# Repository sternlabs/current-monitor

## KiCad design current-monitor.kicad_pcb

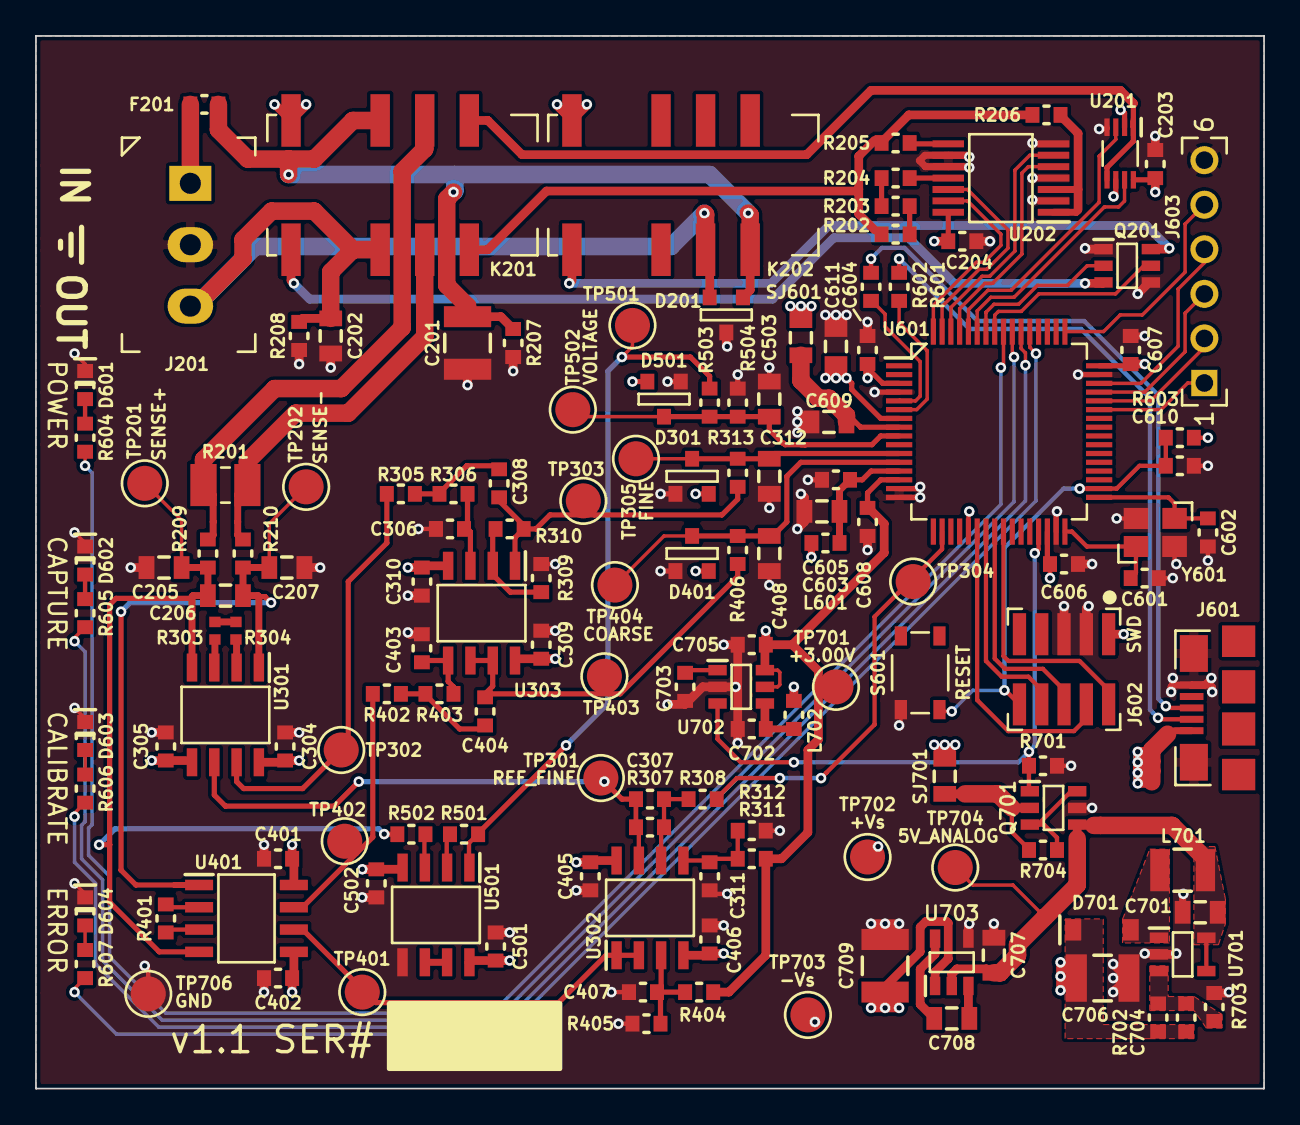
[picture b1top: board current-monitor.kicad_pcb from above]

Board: 4 copper layers, 70.0 x 60.0 mm, 143 parts (0 on the bottom side), 93 nets.

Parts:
C201, C706, C709: 10u; SMD-3225
C202, C603, C609, C611, C701, C707, C708: 2.2u; SMD-2012
C203, C204, C304, C305, C309, C310, C401, C402, C405, C406, C501, C502, C604, C605, C606, C607, C608, C610, C702, C705: 0.1u; SMD-1608
C205, C207, C312, C408, C503: 4.7n; SMD-2012
C206: 47n; SMD-2012
C306, C308, C404: 1n; SMD-1608
C307: 470p; SMD-1608
C311, C407, C703: 10n; SMD-1608
C403: 120p; SMD-1608
C601, C602: 8p; SMD-1608
C704: 134p; SMD-1608
D201: MMBZ15VALT1G; SOT-23
D301, D401, D501: BAS40-04; SOT-23
D601: POWER; SMD-1608-LED
D602: ERROR; SMD-1608-LED
D603: CAPTURE; SMD-1608-LED
D604: CALIBRATE; SMD-1608-LED
D701: MBR0530; SOD-123
F201: 2A; SMD-1608
J201: CONN-3; TERM-3-3.5-PTH
J601: USB-MICROB; USB-MICRO-B-FCI-10118192
J602: SWD; CONN-2x5-1.27-SMT
J603: CONN-6; CONN-6-2.54-1.0-PTH
K201, K202: RELAY-DPDT-EE2-SPLIT; RELAY-EE2-NU
L601, L702: MPZ1608B471ATA00; SMD-1608
L701: 33u 0.2A; SMD-2520
Q201: DRDC3105E6; SOT-23-6
Q701: DMG6601LVT; SOT-23-6
R201: 0.33; KRL2012D
R202, R203, R204: 470k 0.05%; SMD-1608
R205: 16k 0.05%; SMD-1608
R206: 150 0.05%; SMD-1608
R207, R208: 470k; SMD-1608
R209, R210: 10; SMD-1608
R303, R304: 0.33; SMD-1005
R305: 4.9k; SMD-1608
R306: 2.36k; SMD-1608
R307: 12k; SMD-1608
R308, R312, R603: 10k; SMD-1608
R309: 4.7k; SMD-1608
R310: 9.4k; SMD-1608
R311: 27k; SMD-1608
R313, R406: 971; SMD-1608
R401: 1.74k; SMD-1608
R402: 6.66k; SMD-1608
R403: 14.5k; SMD-1608
R404: 67k; SMD-1608
R405: 499; SMD-1608
R501, R502: 20k; SMD-1608
R503: 4k; SMD-1608
R504, R604, R605, R606, R607: 1k; SMD-1608
R601, R602: 33; SMD-1608
R701, R704: 51k; SMD-1608
R702: 149k; SMD-1608
R703: 13.3k; SMD-1608
S601: RESET; TACT-4632
SJ601: SENSE_MCU; SMD-2012
SJ701: SENSE_ANALOG; SMD-2012
TP201: SENSE+; TESTPOINT-2.0
TP202: SENSE-; TESTPOINT-2.0
TP301: REF_FINE; TESTPOINT-2.0
TP302: FINE_LOW; TESTPOINT-2.0
TP303: FINE_UNCLAMPED; TESTPOINT-2.0
TP304: REF_ADJUST; TESTPOINT-2.0
TP305: FINE; TESTPOINT-2.0
TP401: REF_COARSE; TESTPOINT-2.0
TP402: COARSE_LOW; TESTPOINT-2.0
TP403: COARSE_UNCLAMPED; TESTPOINT-2.0
TP404: COARSE; TESTPOINT-2.0
TP501: VOLTAGE_RAW; TESTPOINT-2.0
TP502: VOLTAGE; TESTPOINT-2.0
TP701: +3.00V; TESTPOINT-2.0
TP702: +Vs; TESTPOINT-2.0
TP703: -Vs; TESTPOINT-2.0
TP704: 5V_ANALOG; TESTPOINT-2.0
TP706: GND; TESTPOINT-2.0
U201: FSA1259A; VFSOP-8
U202: MAX4737EUD; TSSOP-14
U301: AD8429A; SOIC-8-N
U302, U501: TL032C; SOIC-8-N
U303: LM833; SOIC-8-N
U401: INA826; SOIC-8-N
U601: K22F-64LQFP; QFP-64-10x10
U701: LM27313; SOT-23-5
U702: MAX6070; SOT-23-6
U703: TPS6040x; SOT-23-5
Y601: 10MHz; OSC3225

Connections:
+3.00V: C608.1, C705.1, R311.2, R404.2, TP701.TP, U201.6, U601.14, U702.5, U702.6
+3V3: C604.1, C606.1, C607.1, C611.1, D301.2, D401.2, D501.2, J602.1, L601.1, R603.1, U601.3, U601.7, U601.21, U601.30, U601.48
+5V: C203.1, C204.1, J601.1, K201.1, K202.1, L702.1, SJ601.1, SJ701.1, U201.2, U201.8, U202.14
+Vs: C304.1, C309.1, C401.1, C405.1, C501.1, C704.1, C706.1, D701.C, R702.1, TP702.TP, U301.8, U302.8, U303.8, U401.8, U501.8
-Vs: C305.1, C310.1, C402.1, C406.1, C502.1, C709.1, TP703.TP, U301.5, U302.4, U303.4, U401.5, U501.4, U703.1
/Current Sense Coarse Range/COARSE_UNCLAMPED: C404.2, R406.1, TP403.TP, U303.6, U303.7
/Current Sense Coarse Range/COARSE_UNFILTERED: R402.1, TP402.TP, U401.7
/Current Sense Coarse Range/REF_COARSE: TP401.TP, U302.1, U302.2, U401.6
/Current Sense Coarse Range/SENSE_COARSE: C408.1, D401.3, R406.2, TP404.TP, U601.12
/Current Sense Fine Range/FINE_UNCLAMPED: C308.2, R310.2, R313.1, TP303.TP, U303.1
/Current Sense Fine Range/REF_ADJUST: R308.2, TP304.TP, U601.18
/Current Sense Fine Range/REF_FINE: C307.1, R307.1, TP301.TP, U301.6, U302.7
/Current Sense Fine Range/SENSE_FINE: C312.1, D301.3, R313.2, TP305.TP, U601.11
/In/Out, Shunt, Calibration/CALIBRATE_3V: U201.3, U601.60
/In/Out, Shunt, Calibration/CALIBRATE_3uA: U202.12, U601.63
/In/Out, Shunt, Calibration/CALIBRATE_5V: U201.7, U601.59
/In/Out, Shunt, Calibration/CALIBRATE_30mA: U202.13, U601.64
/In/Out, Shunt, Calibration/CALIBRATE_30mA_2: U202.5, U601.61
/In/Out, Shunt, Calibration/CALIBRATE_300uA: U202.6, U601.62
/In/Out, Shunt, Calibration/IN: C201.1, D201.1, F201.1, K201.3, K202.8, R207.1
/In/Out, Shunt, Calibration/OUT: C202.1, D201.2, J201.3, K201.10, K202.9, R208.1
/In/Out, Shunt, Calibration/RELAY_CALIBRATE: Q201.2, U601.58
/In/Out, Shunt, Calibration/RELAY_INOUT_SHORT: Q201.5, U601.57
/MCU/5V_MCU: C609.1, SJ601.2, U601.8
/MCU/GPIO0: J603.1, U601.43
/MCU/GPIO1: J603.2, U601.44
/MCU/GPIO2: J603.3, U601.45
/MCU/GPIO3: J603.4, U601.46
/MCU/GPIO4: J603.5, U601.49
/MCU/LED_CALIBRATE: R606.1, U601.54
/MCU/LED_CAPTURE: R605.1, U601.55
/MCU/LED_ERROR: R607.1, U601.53
/MCU/LED_POWER: R604.1, U601.56
/MCU/SENSE_VOLTAGE: C503.1, D501.3, R503.2, R504.1, TP502.TP, U601.9
/MCU/SWD_CLK: J602.4, U601.22
/MCU/SWD_DIO: J602.2, U601.25
/MCU/UART_RX: J602.8, U601.23
/MCU/UART_TX: J602.6, U601.24
/MCU/USB_DM: J601.2, R601.1
/MCU/USB_DP: J601.3, R602.1
/MCU/VS_ENABLE: Q701.1, R701.1, U601.29, U702.3
/MCU/~RESET: C610.1, J602.10, R603.2, S601.3, U601.34
/Power Supply/5V_ANALOG: C701.1, C707.1, L701.1, Q701.4, TP704.TP, U701.4, U701.5, U703.2
/Power Supply/DC_FB: C704.2, R702.2, R703.1, U701.3
/Power Supply/DC_SW: D701.A, L701.2, U701.1
/Sense Voltage/VOLTAGE_RAW: R501.1, R503.1, TP501.TP, U501.1
COM: C201.2, C202.2, C203.2, C204.2, C205.2, C207.2, C304.2, C305.2, C306.2, C309.2, C310.2, C311.2, C312.2, C401.2, C402.2, C403.2, C405.2, C406.2, C407.2, C408.2, C501.2, C502.2, C503.2, C601.2, C602.2, C603.2, C604.2, C605.2, C606.2, C607.2, C608.2, C609.2, C610.2, C611.2, C701.2, C702.2, C703.2, C705.2, C706.2, C707.2, C709.2, D201.3, D301.1, D401.1, D501.1, D601.C, D602.C, D603.C, D604.C, J201.2, J601.5, J601.SHIE, J602.3, J602.5, J603.6, Q201.1, Q201.4, Q701.5, R207.2, R208.2, R309.2, R312.2, R405.2, R504.2, R701.2, R703.2, S601.1, TP706.TP, U201.4, U202.2, U202.4, U202.7, U202.9, U202.10, U501.5, U601.4, U601.15, U601.16, U601.31, U601.47, U701.2, U702.2, U703.4, Y601.2, Y601.4
unnamed: C306.1, R306.2, U303.3
unnamed: C307.2, R307.2, R308.1, U302.6
unnamed: C308.1, R305.2, R306.1
unnamed: C311.1, R311.1, R312.1, U302.5
unnamed: C403.1, R403.2, U303.5
unnamed: C404.1, R402.2, R403.1
unnamed: C407.1, R404.1, R405.1, U302.3
unnamed: C601.1, U601.32, Y601.1
unnamed: C602.1, U601.33, Y601.3
unnamed: C603.1, C605.1, L601.2, U601.13
unnamed: C702.1, L702.2, U702.4
unnamed: C703.1, U702.1
unnamed: C708.1, U703.3
unnamed: C708.2, U703.5
unnamed: D601.A, R604.2
unnamed: D602.A, R605.2
unnamed: D603.A, R606.2
unnamed: D604.A, R607.2
unnamed: F201.2, J201.1
unnamed: K201.4, R201.1, R209.1
unnamed: K201.5, U201.1, U201.5
unnamed: K201.8, R202.1, R205.1, R206.1
unnamed: K201.9, R201.2, R210.1
unnamed: K201.12, Q201.3
unnamed: K202.12, Q201.6
unnamed: Q701.2, R704.1, SJ701.2
unnamed: Q701.3, Q701.6, R704.2
unnamed: R202.2, R203.1
unnamed: R203.2, R204.1
unnamed: R204.2, U202.11
unnamed: R205.2, U202.8
unnamed: R206.2, U202.1, U202.3
unnamed: R303.1, U301.3
unnamed: R303.2, R304.1
unnamed: R304.2, U301.2
unnamed: R305.1, TP302.TP, U301.7
unnamed: R309.1, R310.1, U303.2
unnamed: R401.1, U401.3
unnamed: R401.2, U401.2
unnamed: R501.2, U501.2
unnamed: R502.2, U501.3
unnamed: R601.2, U601.6
unnamed: R602.2, U601.5
unnamed: U501.6, U501.7
SENSE+: C205.1, C206.1, R209.2, R502.1, TP201.TP, U301.4, U401.4
SENSE-: C206.2, C207.1, R210.2, TP202.TP, U301.1, U401.1

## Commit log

2015-08-18 start schematic
2015-08-21 close to functional
2015-08-23 more layout
2015-08-24 add ltc6102
2015-08-25 add calibration
2015-08-25 remove ltc6102 again
2015-08-25 shuffle, prettify schematic
2015-08-25 shuffle sheet numbers
2015-08-25 renumber pmos
2015-08-25 renumber, add calibration relays
2015-08-25 renumber pcb
2015-08-25 use screw terminals
2015-09-03 add analog switches
2015-09-03 add current sense jumpers
2015-09-08 checkpoint
2015-09-08 full design
2015-09-08 adjust mask clearance
2015-09-11 zone connections
2015-09-11 move Q201 to the east
2015-09-13 use rfi filter for all inputs
2015-09-13 case size pass
2015-09-15 change footprints
2015-09-15 adapt layout
2015-09-15 add maxima filter calculations
2015-09-15 change fill
2015-09-15 board size mod
2015-09-15 layout finish
2015-09-15 1.0-rc1
2015-09-15 silkscreen
2015-09-15 move SJ for mcu
2015-09-15 tidy up power plane
2015-09-15 slight track cleanup
2015-09-16 fix BOM number
2015-09-16 adjust filter calcs for 20kHz
2015-09-18 change power supply
2015-09-18 pcb cleanup
2015-09-18 remove dangling via
2015-09-18 move via
2015-09-18 thermal relief on input gnd
2015-09-21 remove power from boost regulator
2015-09-25 venable switches vref as well
2015-09-28 add 3d shapes
2015-10-16 add forgotten via

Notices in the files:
current-monitor.kicad_pcb:
(c) 2015 Simon Schubert
